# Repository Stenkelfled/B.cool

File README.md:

# iceceb
intelligent crate for ensuring cold and enjoyable beer

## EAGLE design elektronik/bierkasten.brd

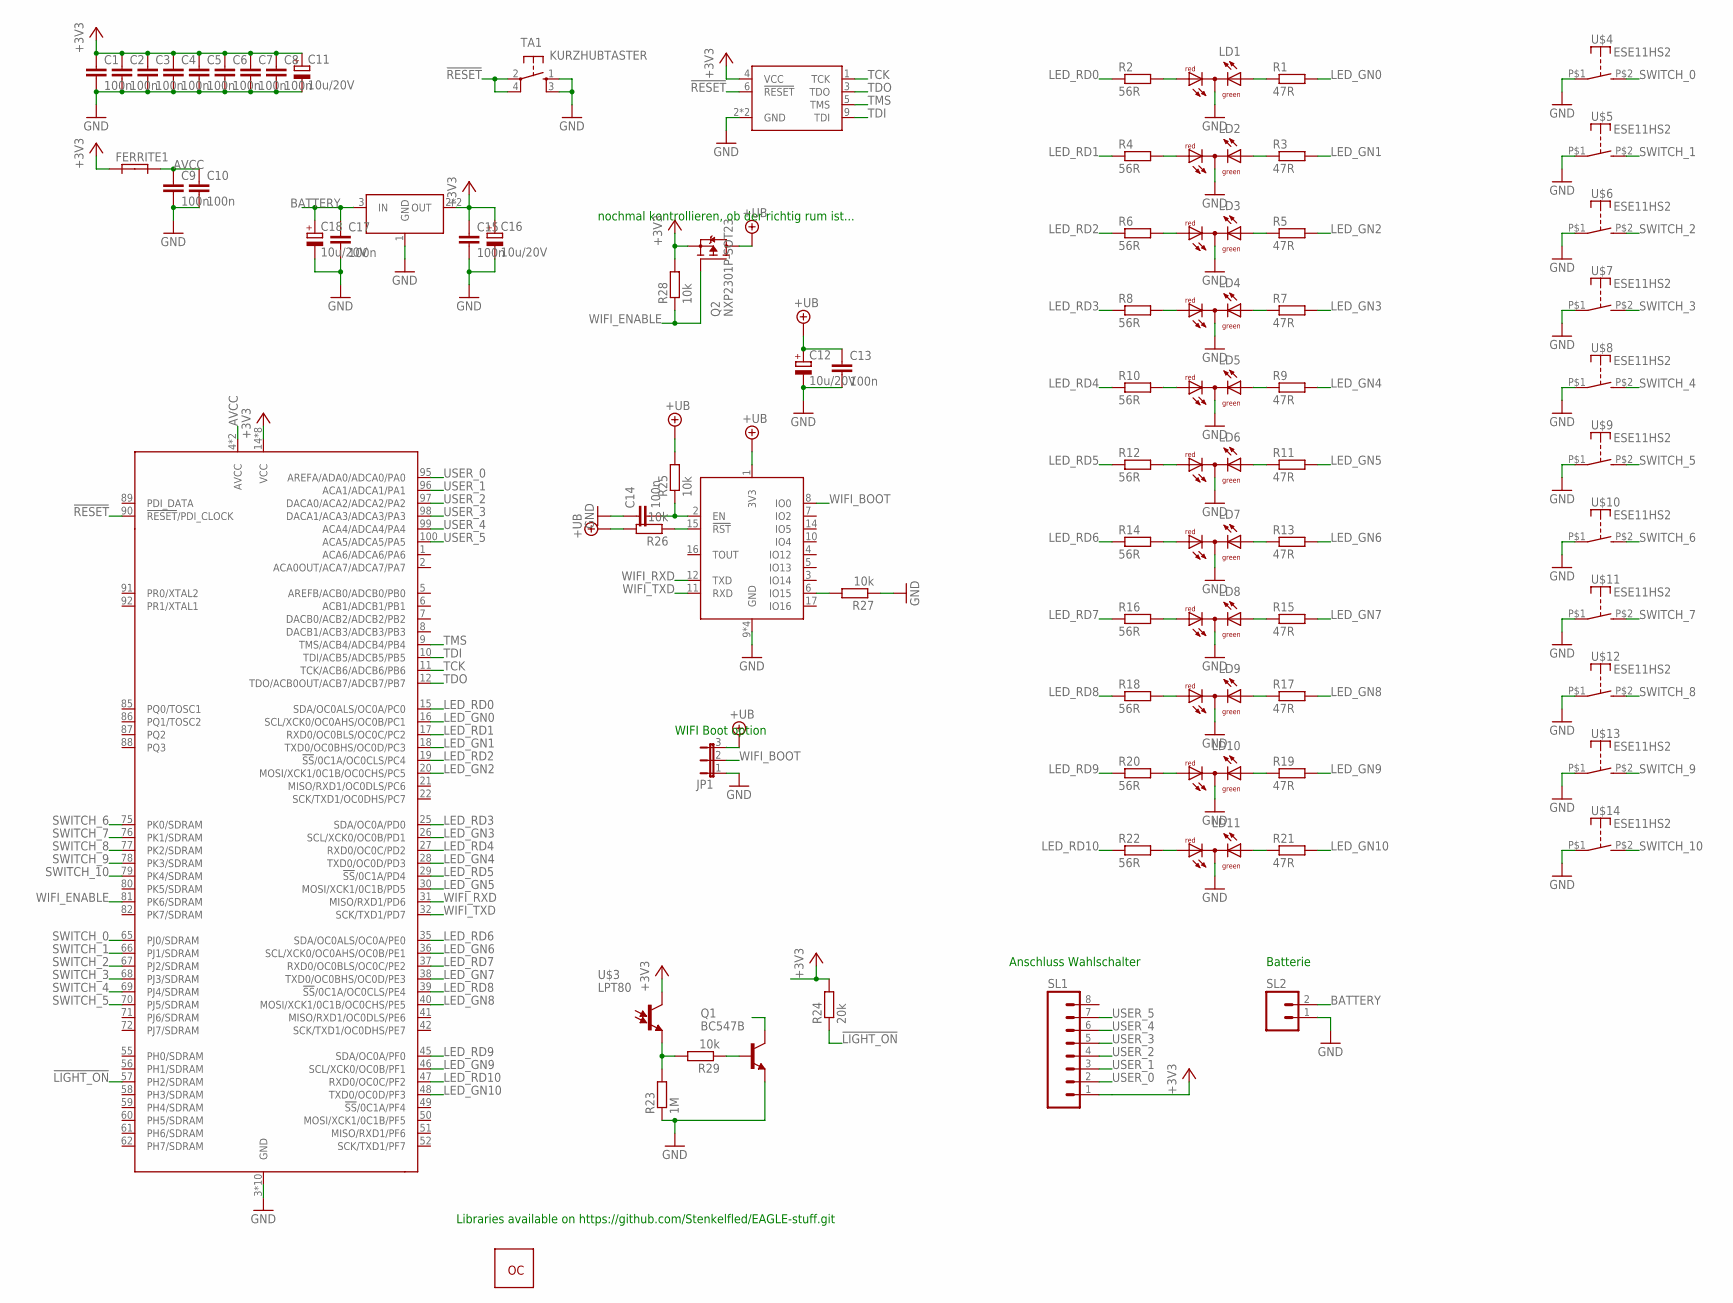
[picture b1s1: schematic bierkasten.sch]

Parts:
C1, C2, C3, C4, C5, C6, C7, C8, C9, C10, C13, C14, C15, C17: 100n; C0603; FARNELL 432210
C11, C12, C16, C18: 10u/20V; B/3528-21W
FERRITE1: FERRITE-EU_0805; L0805
JP1: JP2E; JP2
LD1, LD2, LD3, LD4, LD5, LD6, LD7, LD8, LD9, LD10, LD11: DUOLED-RG-C-WIRE; DUOLED-C-WIRE
Q1: BC547B; TO92
Q2: NXP2301P-SOT23; SOT23
R1, R3, R5, R7, R9, R11, R13, R15, R17, R19, R21: 47R; R0603; FARNELL 2502461
R2, R4, R6, R8, R10, R12, R14, R16, R18, R20, R22: 56R; R0603
R23: 1M; R0603
R24: 20k; R0603
R25, R26, R27, R28: 10k; R0603; FARNELL 2502397
R29: 10k; R0603
SL1: M08; 08P
SL2: M02; 02P
TA1: KURZHUBTASTER; TA93XX; FARNELL 2292960
U$1: ATXMEGA_A1; TQFP100
U$2: AVR-JTAG-10; WANNE10G
U$3: LPT80
U$4, U$5, U$6, U$7, U$8, U$9, U$10, U$11, U$12, U$13, U$14: ESE11HS2; 2X2,54
U$15: ESP8266-POLLIN
U$16: NCP1117ST33T3G; SOT223
U$17: BESTELLTEILE

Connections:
!LIGHT_ON: R24.1, U$1.57 (PH2/SDRAM)
!RESET: TA1.2, TA1.4 (P1), U$1.90 (!RESET!/PDI_CLOCK), U$2.6 (!RESET)
+3V3: C1.1, C2.1, C3.1, C4.1, C5.1, C6.1, C7.1, C8.1, C11.+, C15.1, C16.+, FERRITE1.1, Q2.2 (S), R24.2, R28.2, SL1.1, U$1.14 (VCC), U$1.24 (VCC), U$1.34 (VCC), U$1.44 (VCC), U$1.54 (VCC), U$1.64 (VCC), U$1.74 (VCC), U$1.83 (VCC), U$2.4 (VCC), U$3.C, U$16.2 (OUT), U$16.4 (OUT)
+UB: C12.+, C13.1, JP1.3, Q2.3 (D), R25.2, R26.2, U$15.1 (3V3)
AVCC: C9.1, C10.1, FERRITE1.2, U$1.4 (AVCC), U$1.94 (AVCC)
BATTERY: C17.1, C18.+, SL2.2, U$16.3 (IN)
GND: C1.2, C2.2, C3.2, C4.2, C5.2, C6.2, C7.2, C8.2, C9.2, C10.2, C11.-, C12.-, C13.2, C14.1, C15.2, C16.-, C17.2, C18.-, JP1.1, LD1.C, LD2.C, LD3.C, LD4.C, LD5.C, LD6.C, LD7.C, LD8.C, LD9.C, LD10.C, LD11.C, Q1.1 (E), R23.1, R27.1, SL2.1, TA1.1 (S), TA1.3 (S1), U$1.3 (GND), U$1.13 (GND), U$1.23 (GND), U$1.33 (GND), U$1.43 (GND), U$1.53 (GND), U$1.63 (GND), U$1.73 (GND), U$1.84 (GND), U$1.93 (GND), U$2.2 (GND), U$2.10 (GND), U$4.P$1, U$5.P$1, U$6.P$1, U$7.P$1, U$8.P$1, U$9.P$1, U$10.P$1, U$11.P$1, U$12.P$1, U$13.P$1, U$14.P$1, U$15.9 (GND), U$15.13 (GND), U$15.18 (GND), U$15.19 (GND), U$16.1 (GND)
LED_GN0: R1.2, U$1.16 (SCL/XCK0/OC0AHS/OC0B/PC1)
LED_GN1: R3.2, U$1.18 (TXD0/OC0BHS/OC0D/PC3)
LED_GN2: R5.2, U$1.20 (MOSI/XCK1/0C1B/OC0CHS/PC5)
LED_GN3: R7.2, U$1.26 (SCL/XCK0/OC0B/PD1)
LED_GN4: R9.2, U$1.28 (TXD0/OC0D/PD3)
LED_GN5: R11.2, U$1.30 (MOSI/XCK1/0C1B/PD5)
LED_GN6: R13.2, U$1.36 (SCL/XCK0/OC0AHS/OC0B/PE1)
LED_GN7: R15.2, U$1.38 (TXD0/OC0BHS/OC0D/PE3)
LED_GN8: R17.2, U$1.40 (MOSI/XCK1/0C1B/OC0CHS/PE5)
LED_GN9: R19.2, U$1.46 (SCL/XCK0/OC0B/PF1)
LED_GN10: R21.2, U$1.48 (TXD0/OC0D/PF3)
LED_RD0: R2.1, U$1.15 (SDA/OC0ALS/OC0A/PC0)
LED_RD1: R4.1, U$1.17 (RXD0/OC0BLS/OC0C/PC2)
LED_RD2: R6.1, U$1.19 (!SS!/0C1A/OC0CLS/PC4)
LED_RD3: R8.1, U$1.25 (SDA/OC0A/PD0)
LED_RD4: R10.1, U$1.27 (RXD0/OC0C/PD2)
LED_RD5: R12.1, U$1.29 (!SS!/0C1A/PD4)
LED_RD6: R14.1, U$1.35 (SDA/OC0ALS/OC0A/PE0)
LED_RD7: R16.1, U$1.37 (RXD0/OC0BLS/OC0C/PE2)
LED_RD8: R18.1, U$1.39 (!SS!/0C1A/OC0CLS/PE4)
LED_RD9: R20.1, U$1.45 (SDA/OC0A/PF0)
LED_RD10: R22.1, U$1.47 (RXD0/OC0C/PF2)
unnamed: LD1.AR, R2.2
unnamed: LD1.AX (AG), R1.1
unnamed: LD2.AR, R4.2
unnamed: LD2.AX (AG), R3.1
unnamed: LD3.AR, R6.2
unnamed: LD3.AX (AG), R5.1
unnamed: LD4.AR, R8.2
unnamed: LD4.AX (AG), R7.1
unnamed: LD5.AR, R10.2
unnamed: LD5.AX (AG), R9.1
unnamed: LD6.AR, R12.2
unnamed: LD6.AX (AG), R11.1
unnamed: LD7.AR, R14.2
unnamed: LD7.AX (AG), R13.1
unnamed: LD8.AR, R16.2
unnamed: LD8.AX (AG), R15.1
unnamed: LD9.AR, R18.2
unnamed: LD9.AX (AG), R17.1
unnamed: LD10.AR, R20.2
unnamed: LD10.AX (AG), R19.1
unnamed: LD11.AR, R22.2
unnamed: LD11.AX (AG), R21.1
unnamed: R23.2, R29.2, U$3.E
unnamed: C14.2, R25.1, U$15.2 (EN)
unnamed: R27.2, U$15.6 (IO15)
unnamed: R26.1, U$15.15 (!RST)
unnamed: Q1.2 (B), R29.1
SWITCH_0: U$1.65 (PJ0/SDRAM), U$4.P$2 (S)
SWITCH_1: U$1.66 (PJ1/SDRAM), U$5.P$2 (S)
SWITCH_2: U$1.67 (PJ2/SDRAM), U$6.P$2 (S)
SWITCH_3: U$1.68 (PJ3/SDRAM), U$7.P$2 (S)
SWITCH_4: U$1.69 (PJ4/SDRAM), U$8.P$2 (S)
SWITCH_5: U$1.70 (PJ5/SDRAM), U$9.P$2 (S)
SWITCH_6: U$1.75 (PK0/SDRAM), U$10.P$2 (S)
SWITCH_7: U$1.76 (PK1/SDRAM), U$11.P$2 (S)
SWITCH_8: U$1.77 (PK2/SDRAM), U$12.P$2 (S)
SWITCH_9: U$1.78 (PK3/SDRAM), U$13.P$2 (S)
SWITCH_10: U$1.79 (PK4/SDRAM), U$14.P$2 (S)
TCK: U$1.11 (TCK/ACB6/ADCB6/PB6), U$2.1 (TCK)
TDI: U$1.10 (TDI/ACB5/ADCB5/PB5), U$2.9 (TDI)
TDO: U$1.12 (TDO/ACB0OUT/ACB7/ADCB7/PB7), U$2.3 (TDO)
TMS: U$1.9 (TMS/ACB4/ADCB4/PB4), U$2.5 (TMS)
USER_0: SL1.2, U$1.95 (AREFA/ADA0/ADCA0/PA0)
USER_1: SL1.3, U$1.96 (ACA1/ADCA1/PA1)
USER_2: SL1.4, U$1.97 (DACA0/ACA2/ADCA2/PA2)
USER_3: SL1.5, U$1.98 (DACA1/ACA3/ADCA3/PA3)
USER_4: SL1.6, U$1.99 (ACA4/ADCA4/PA4)
USER_5: SL1.7, U$1.100 (ACA5/ADCA5/PA5)
WIFI_BOOT: JP1.2, U$15.8 (IO0)
WIFI_ENABLE: Q2.1 (G), R28.1, U$1.81 (PK6/SDRAM)
WIFI_RXD: U$1.31 (MISO/RXD1/PD6), U$15.12 (TXD)
WIFI_TXD: U$1.32 (SCK/TXD1/PD7), U$15.11 (RXD)

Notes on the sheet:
Libraries available on https://github.com/Stenkelfled/EAGLE-stuff.git
WIFI Boot option
Anschluss Wahlschalter
nochmal kontrollieren, ob der richtig rum ist...
Batterie

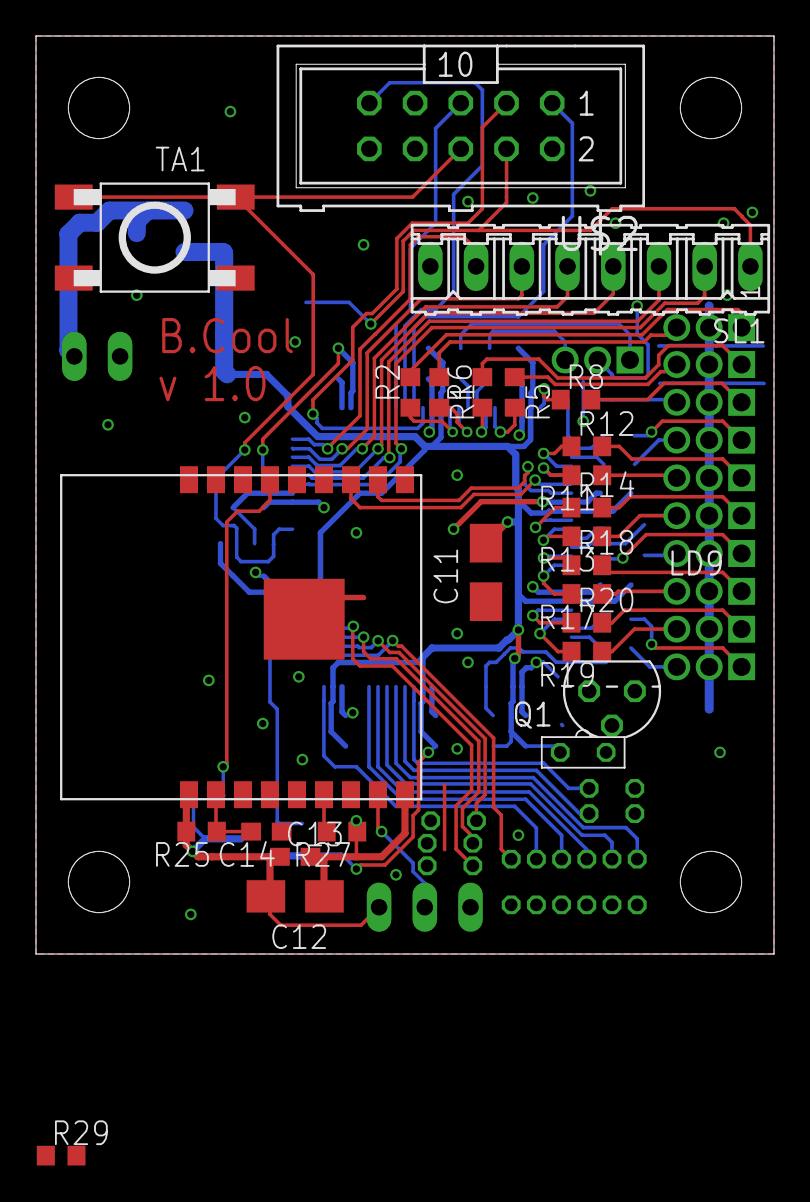
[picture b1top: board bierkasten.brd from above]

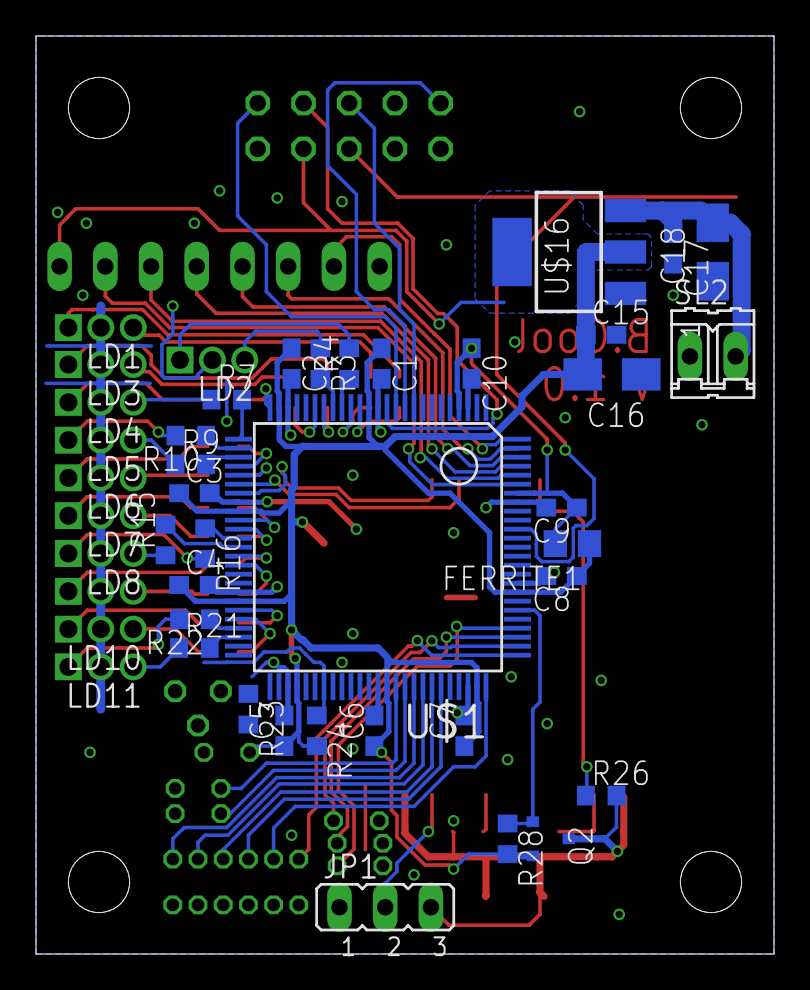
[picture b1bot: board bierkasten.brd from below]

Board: 2 copper layers, 41.0 x 51.0 mm, 82 parts (55 on the bottom side), 81 nets.

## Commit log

2018-08-06 UDP-Kommunkation mit Python funktioniert
2018-08-06 Gitignore angepasst
2018-08-17 Bestellnummern für Bauteile vorgemerkt
2018-08-17 Datenblatt
2018-08-17 Anfänge des Schaltplans
2018-08-17 Bestellcodes fertig gemacht
2018-08-17 Kommandosammlung für den ESP8266
2018-08-19 Stecker für User-Wahlschalter hinzugefügt.
2018-09-08 Schaltplan fertig
2018-09-28 Layout fertig
2018-09-28 Fertigungsdaten erstellt
2018-09-28 Ärger mit den Bordaten behoben. PCB bestellt.
2018-10-28 Add firmware AtmelStudio-Project
2018-10-28 re-organize datasheets
2018-11-04 Add Port-initialization for BeerSlots
2018-11-04 Initialization for Beer LED-Timers
2018-11-10 Add LED color definition
2018-11-18 Add LED initialization
2018-12-23 WIP: add RTC-timer
2018-12-31 Add RTC and handle for pinChangeInterrupt
2019-01-01 Add Power management
2019-01-01 Set LED color by time
2019-01-27 First test: successful
    * LED goes green, when bottle is inserted and off, when bottle is
    removed
    * No timing via RTC, no sleeping, but LEDs are controlled via Timer and
    PWM
2019-01-27 LEDs now light in the proper color
    * However, Updating the LEDs is still a problem.
2019-01-29 Preparetion for sleep: Light detection now working
    * Plus: The LED-Updates now takes place in main - not in interrupt
2019-01-29 Enabled Sleep
2019-01-29 Add User switch
2019-09-13 Light detection has its own PCB
2019-09-13 Adjust LED brightness
